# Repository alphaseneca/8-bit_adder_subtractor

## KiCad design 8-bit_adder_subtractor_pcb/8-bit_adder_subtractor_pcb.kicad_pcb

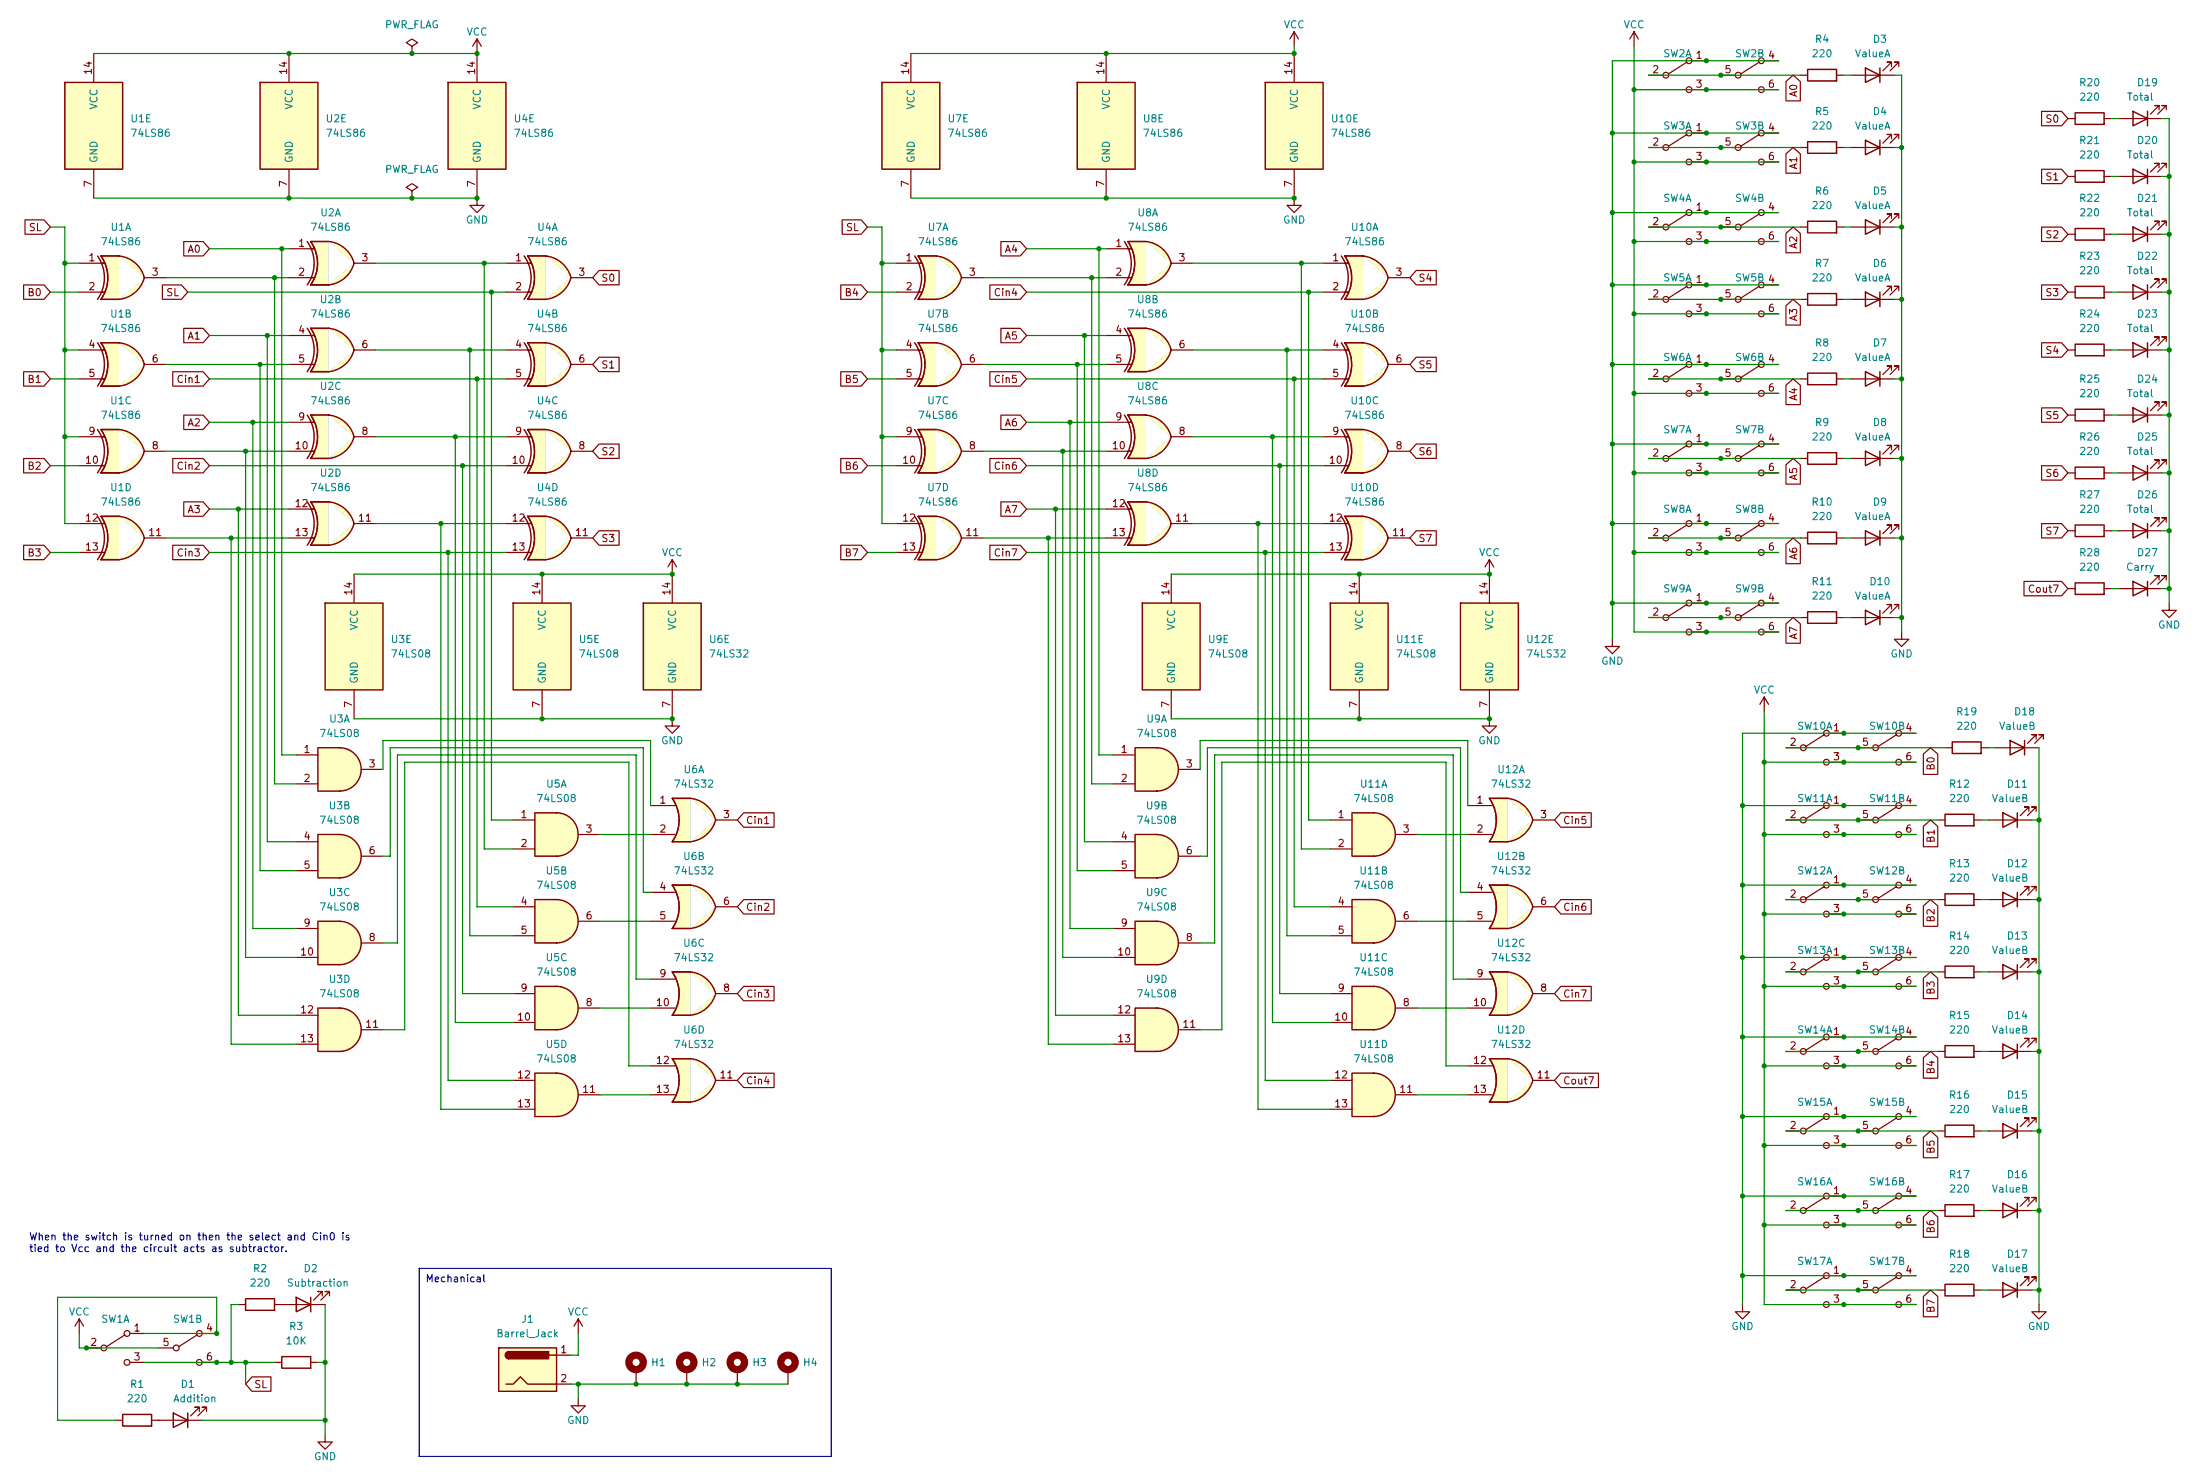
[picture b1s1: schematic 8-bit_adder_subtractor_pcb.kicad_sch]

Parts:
D1: Addition; LED_D3.0mm
D2: Subtraction; LED_D3.0mm
D3, D4, D5, D6, D7, D8, D9, D10: ValueA; LED_D3.0mm
D11, D12, D13, D14, D15, D16, D17, D18: ValueB; LED_D3.0mm
D19, D20, D21, D22, D23, D24, D25, D26: Total; LED_D3.0mm
D27: Carry; LED_D3.0mm
H1, H2, H3, H4: MountingHole_Pad; MountingHole_3mm_Pad
J1: Barrel_Jack; BarrelJack_Horizontal
R1, R2, R4, R5, R6, R7, R8, R9, R10, R11, R12, R13, R14, R15, R16, R17, R18, R19, R20, R21, R22, R23, R24, R25, R26, R27, R28: 220; R_Axial_DIN0207_L6.3mm_D2.5mm_P7.62mm_Horizontal
R3: 10K; R_Axial_DIN0207_L6.3mm_D2.5mm_P7.62mm_Horizontal
SW1, SW2, SW3, SW4, SW5, SW6, SW7, SW8, SW9, SW10, SW11, SW12, SW13, SW14, SW15, SW16, SW17: SW_DPDT_x2; SWITCH_S20203
U1, U2, U4, U7, U8, U10: 74LS86; DIP-14_W7.62mm
U3, U5, U9, U11: 74LS08; DIP-14_W7.62mm
U6, U12: 74LS32; DIP-14_W7.62mm

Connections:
A0: R4.1, SW2.2 (B), SW2.5 (B), U2.1, U3.1; also elsewhere on the board
A1: R5.1, SW3.2 (B), SW3.5 (B), U2.4, U3.4; also elsewhere on the board
A2: R6.1, SW4.2 (B), SW4.5 (B), U2.9, U3.9; also elsewhere on the board
A3: R7.1, SW5.2 (B), SW5.5 (B), U2.12, U3.12; also elsewhere on the board
A4: R8.1, SW6.2 (B), SW6.5 (B), U8.1, U9.1; also elsewhere on the board
A5: R9.1, SW7.2 (B), SW7.5 (B), U8.4, U9.4; also elsewhere on the board
A6: R10.1, SW8.2 (B), SW8.5 (B), U8.9, U9.9; also elsewhere on the board
A7: R11.1, SW9.2 (B), SW9.5 (B), U8.12, U9.12; also elsewhere on the board
B0: R19.1, SW10.2 (B), SW10.5 (B), U1.2; also elsewhere on the board
B1: R12.1, SW11.2 (B), SW11.5 (B), U1.5; also elsewhere on the board
B2: R13.1, SW12.2 (B), SW12.5 (B), U1.10; also elsewhere on the board
B3: R14.1, SW13.2 (B), SW13.5 (B), U1.13; also elsewhere on the board
B4: R15.1, SW14.2 (B), SW14.5 (B), U7.2; also elsewhere on the board
B5: R16.1, SW15.2 (B), SW15.5 (B), U7.5; also elsewhere on the board
B6: R17.1, SW16.2 (B), SW16.5 (B), U7.10; also elsewhere on the board
B7: R18.1, SW17.2 (B), SW17.5 (B), U7.13; also elsewhere on the board
Cin1: U4.5, U5.4, U6.3; also elsewhere on the board
Cin2: U4.10, U5.9, U6.6; also elsewhere on the board
Cin3: U4.13, U5.12, U6.8; also elsewhere on the board
Cin4: U6.11, U10.2, U11.1; also elsewhere on the board
Cin5: U10.5, U11.4, U12.3; also elsewhere on the board
Cin6: U10.10, U11.9, U12.6; also elsewhere on the board
Cin7: U10.13, U11.12, U12.8; also elsewhere on the board
Cout7: R28.1, U12.11; also elsewhere on the board
GND: D1.1 (K), D2.1 (K), D3.1 (K), D4.1 (K), D5.1 (K), D6.1 (K), D7.1 (K), D8.1 (K), D9.1 (K), D10.1 (K), D11.1 (K), D12.1 (K), D13.1 (K), D14.1 (K), D15.1 (K), D16.1 (K), D17.1 (K), D18.1 (K), D19.1 (K), D20.1 (K), D21.1 (K), D22.1 (K), D23.1 (K), D24.1 (K), D25.1 (K), D26.1 (K), D27.1 (K), H1.1, H2.1, H3.1, H4.1, J1.2, R3.2, SW2.1 (A), SW2.4 (A), SW3.1 (A), SW3.4 (A), SW4.1 (A), SW4.4 (A), SW5.1 (A), SW5.4 (A), SW6.1 (A), SW6.4 (A), SW7.1 (A), SW7.4 (A), SW8.1 (A), SW8.4 (A), SW9.1 (A), SW9.4 (A), SW10.1 (A), SW10.4 (A), SW11.1 (A), SW11.4 (A), SW12.1 (A), SW12.4 (A), SW13.1 (A), SW13.4 (A), SW14.1 (A), SW14.4 (A), SW15.1 (A), SW15.4 (A), SW16.1 (A), SW16.4 (A), SW17.1 (A), SW17.4 (A), U1.7 (GND), U2.7 (GND), U3.7 (GND), U4.7 (GND), U5.7 (GND), U6.7 (GND), U7.7 (GND), U8.7 (GND), U9.7 (GND), U10.7 (GND), U11.7 (GND), U12.7 (GND); also elsewhere on the board
unnamed: D1.2 (A), R1.2
unnamed: D2.2 (A), R2.2
unnamed: D3.2 (A), R4.2
unnamed: D4.2 (A), R5.2
unnamed: D5.2 (A), R6.2
unnamed: D6.2 (A), R7.2
unnamed: D7.2 (A), R8.2
unnamed: D8.2 (A), R9.2
unnamed: D9.2 (A), R10.2
unnamed: D10.2 (A), R11.2
unnamed: D11.2 (A), R12.2
unnamed: D12.2 (A), R13.2
unnamed: D13.2 (A), R14.2
unnamed: D14.2 (A), R15.2
unnamed: D15.2 (A), R16.2
unnamed: D16.2 (A), R17.2
unnamed: D17.2 (A), R18.2
unnamed: D18.2 (A), R19.2
unnamed: D19.2 (A), R20.2
unnamed: D20.2 (A), R21.2
unnamed: D21.2 (A), R22.2
unnamed: D22.2 (A), R23.2
unnamed: D23.2 (A), R24.2
unnamed: D24.2 (A), R25.2
unnamed: D25.2 (A), R26.2
unnamed: D26.2 (A), R27.2
unnamed: D27.2 (A), R28.2
unnamed: R1.1, SW1.1 (A), SW1.4 (A)
unnamed 53: U1.3, U2.2, U3.2; also elsewhere on the board
unnamed 54: U1.6, U2.5, U3.5; also elsewhere on the board
unnamed 55: U1.8, U2.10, U3.10; also elsewhere on the board
unnamed 56: U1.11, U2.13, U3.13; also elsewhere on the board
unnamed 57: U2.3, U4.1, U5.2; also elsewhere on the board
unnamed 58: U2.6, U4.4, U5.5; also elsewhere on the board
unnamed 59: U2.8, U4.9, U5.10; also elsewhere on the board
unnamed 60: U2.11, U4.12, U5.13; also elsewhere on the board
unnamed 61: U3.3, U6.1; also elsewhere on the board
unnamed 62: U3.6, U6.4; also elsewhere on the board
unnamed 63: U3.8, U6.9; also elsewhere on the board
unnamed 64: U3.11, U6.12; also elsewhere on the board
unnamed 65: U5.3, U6.2; also elsewhere on the board
unnamed 66: U5.6, U6.5; also elsewhere on the board
unnamed 67: U5.8, U6.10; also elsewhere on the board
unnamed 68: U5.11, U6.13; also elsewhere on the board
unnamed 69: U7.3, U8.2, U9.2; also elsewhere on the board
unnamed 70: U7.6, U8.5, U9.5; also elsewhere on the board
unnamed 71: U7.8, U8.10, U9.10; also elsewhere on the board
unnamed 72: U7.11, U8.13, U9.13; also elsewhere on the board
unnamed 73: U8.3, U10.1, U11.2; also elsewhere on the board
unnamed 74: U8.6, U10.4, U11.5; also elsewhere on the board
unnamed 75: U8.8, U10.9, U11.10; also elsewhere on the board
unnamed 76: U8.11, U10.12, U11.13; also elsewhere on the board
unnamed 77: U11.3, U12.2; also elsewhere on the board
unnamed 78: U11.6, U12.5; also elsewhere on the board
unnamed 79: U11.8, U12.10; also elsewhere on the board
unnamed 80: U11.11, U12.13; also elsewhere on the board
unnamed 81: U9.3, U12.1; also elsewhere on the board
unnamed 82: U9.6, U12.4; also elsewhere on the board
unnamed 83: U9.8, U12.9; also elsewhere on the board
unnamed 84: U9.11, U12.12; also elsewhere on the board
S0: R20.1, U4.3; also elsewhere on the board
S1: R21.1, U4.6; also elsewhere on the board
S2: R22.1, U4.8; also elsewhere on the board
S3: R23.1, U4.11; also elsewhere on the board
S4: R24.1, U10.3; also elsewhere on the board
S5: R25.1, U10.6; also elsewhere on the board
S6: R26.1, U10.8; also elsewhere on the board
S7: R27.1, U10.11; also elsewhere on the board
SL: R2.1, R3.1, SW1.3 (C), SW1.6 (C), U1.1, U1.4, U1.9, U1.12, U4.2, U5.1, U7.1, U7.4, U7.9, U7.12; also elsewhere on the board
VCC: J1.1, SW1.2 (B), SW1.5 (B), SW2.3 (C), SW2.6 (C), SW3.3 (C), SW3.6 (C), SW4.3 (C), SW4.6 (C), SW5.3 (C), SW5.6 (C), SW6.3 (C), SW6.6 (C), SW7.3 (C), SW7.6 (C), SW8.3 (C), SW8.6 (C), SW9.3 (C), SW9.6 (C), SW10.3 (C), SW10.6 (C), SW11.3 (C), SW11.6 (C), SW12.3 (C), SW12.6 (C), SW13.3 (C), SW13.6 (C), SW14.3 (C), SW14.6 (C), SW15.3 (C), SW15.6 (C), SW16.3 (C), SW16.6 (C), SW17.3 (C), SW17.6 (C), U1.14 (VCC), U2.14 (VCC), U3.14 (VCC), U4.14 (VCC), U5.14 (VCC), U6.14 (VCC), U7.14 (VCC), U8.14 (VCC), U9.14 (VCC), U10.14 (VCC), U11.14 (VCC), U12.14 (VCC); also elsewhere on the board

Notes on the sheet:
Mechanical
When the switch is turned on then the select and Cin0 is tied to Vcc and the circuit acts as subtractor.

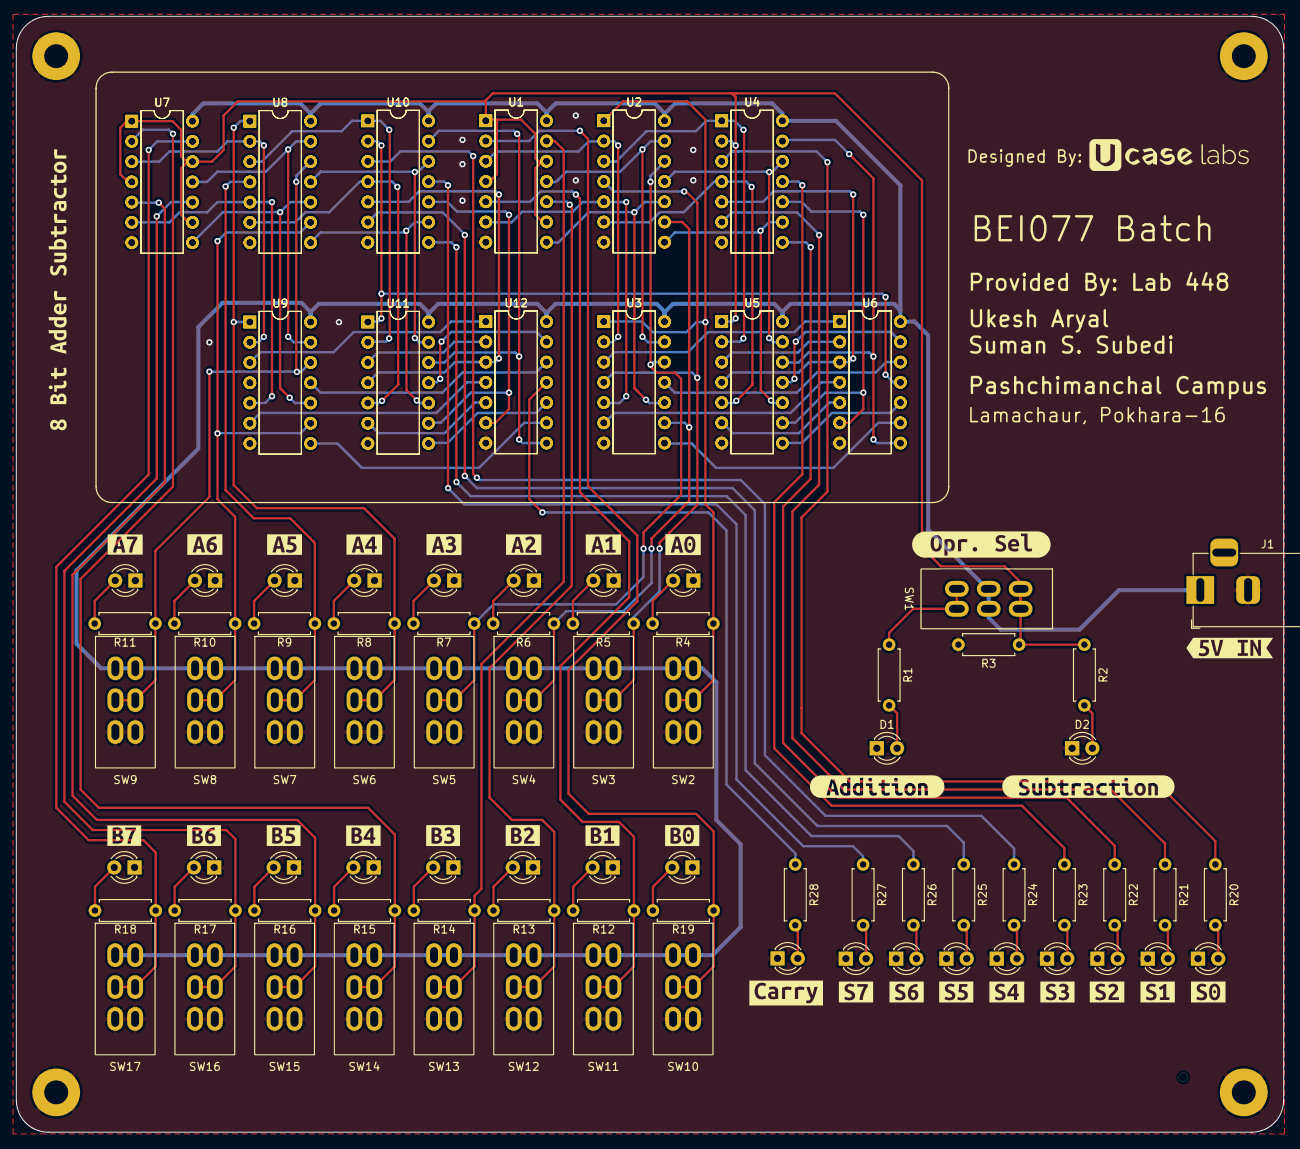
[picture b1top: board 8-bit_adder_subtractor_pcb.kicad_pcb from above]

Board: 2 copper layers, 159.0 x 140.0 mm, 131 parts (0 on the bottom side), 95 nets.

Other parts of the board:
U1#2, U2#2, U4#2, U7#2, U8#2, U10#2: 74LS86; DIP-14_W7.62mm
U3#2, U5#2, U9#2, U11#2: 74LS08; DIP-14_W7.62mm
U6#2, U12#2: 74LS32; DIP-14_W7.62mm
kibuzzard-6723CCFE: G***; kibuzzard-6723CCFE
kibuzzard-6723CD0E: G***; kibuzzard-6723CD0E
kibuzzard-6723CD1A: G***; kibuzzard-6723CD1A
kibuzzard-6723CD2D: G***; kibuzzard-6723CD2D
kibuzzard-6723CD06: G***; kibuzzard-6723CD06
kibuzzard-6723CD14: G***; kibuzzard-6723CD14
kibuzzard-6723CD21: G***; kibuzzard-6723CD21
kibuzzard-6723CD27: G***; kibuzzard-6723CD27
kibuzzard-6723D2BC: G***; kibuzzard-6723D2BC
kibuzzard-6723D2C8: G***; kibuzzard-6723D2C8
kibuzzard-6723D2CE: G***; kibuzzard-6723D2CE
kibuzzard-6723D2D3: G***; kibuzzard-6723D2D3
kibuzzard-6723D2DF: G***; kibuzzard-6723D2DF
kibuzzard-6723D2E6: G***; kibuzzard-6723D2E6
kibuzzard-6723D2EE: G***; kibuzzard-6723D2EE
kibuzzard-6723D31B: G***; kibuzzard-6723D31B
kibuzzard-6723D320: G***; kibuzzard-6723D320
kibuzzard-6723D341: G***; kibuzzard-6723D341
kibuzzard-68098BF2: G***; kibuzzard-68098BF2
kibuzzard-672327BC: G***; kibuzzard-672327BC
kibuzzard-672327C5: G***; kibuzzard-672327C5
kibuzzard-672327D0: G***; kibuzzard-672327D0
kibuzzard-672327D8: G***; kibuzzard-672327D8
kibuzzard-672327DE: G***; kibuzzard-672327DE
kibuzzard-672327E5: G***; kibuzzard-672327E5
kibuzzard-672327EF: G***; kibuzzard-672327EF
kibuzzard-672491A3: G***; kibuzzard-672491A3
kibuzzard-6723279E: G***; kibuzzard-6723279E
kibuzzard-6723280D: G***; kibuzzard-6723280D
kibuzzard-67232848: G***; kibuzzard-67232848

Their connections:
A0: U2#2.1, U3#2.1; also elsewhere on the board
A1: U2#2.4, U3#2.4; also elsewhere on the board
A2: U2#2.9, U3#2.9; also elsewhere on the board
A3: U2#2.12, U3#2.12; also elsewhere on the board
A4: U8#2.1, U9#2.1; also elsewhere on the board
A5: U8#2.4, U9#2.4; also elsewhere on the board
A6: U8#2.9, U9#2.9; also elsewhere on the board
A7: U8#2.12, U9#2.12; also elsewhere on the board
B0: U1#2.2; also elsewhere on the board
B1: U1#2.5; also elsewhere on the board
B2: U1#2.10; also elsewhere on the board
B3: U1#2.13; also elsewhere on the board
B4: U7#2.2; also elsewhere on the board
B5: U7#2.5; also elsewhere on the board
B6: U7#2.10; also elsewhere on the board
B7: U7#2.13; also elsewhere on the board
Cin1: U4#2.5, U5#2.4, U6#2.3; also elsewhere on the board
Cin2: U4#2.10, U5#2.9, U6#2.6; also elsewhere on the board
Cin3: U4#2.13, U5#2.12, U6#2.8; also elsewhere on the board
Cin4: U6#2.11, U10#2.2, U11#2.1; also elsewhere on the board
Cin5: U10#2.5, U11#2.4, U12#2.3; also elsewhere on the board
Cin6: U10#2.10, U11#2.9, U12#2.6; also elsewhere on the board
Cin7: U10#2.13, U11#2.12, U12#2.8; also elsewhere on the board
Cout7: U12#2.11; also elsewhere on the board
GND: U1#2.7 (GND), U2#2.7 (GND), U3#2.7 (GND), U4#2.7 (GND), U5#2.7 (GND), U6#2.7 (GND), U7#2.7 (GND), U8#2.7 (GND), U9#2.7 (GND), U10#2.7 (GND), U11#2.7 (GND), U12#2.7 (GND); also elsewhere on the board
unnamed 53: U1#2.3, U2#2.2, U3#2.2; also elsewhere on the board
unnamed 54: U1#2.6, U2#2.5, U3#2.5; also elsewhere on the board
unnamed 55: U1#2.8, U2#2.10, U3#2.10; also elsewhere on the board
unnamed 56: U1#2.11, U2#2.13, U3#2.13; also elsewhere on the board
unnamed 57: U2#2.3, U4#2.1, U5#2.2; also elsewhere on the board
unnamed 58: U2#2.6, U4#2.4, U5#2.5; also elsewhere on the board
unnamed 59: U2#2.8, U4#2.9, U5#2.10; also elsewhere on the board
unnamed 60: U2#2.11, U4#2.12, U5#2.13; also elsewhere on the board
unnamed 61: U3#2.3, U6#2.1; also elsewhere on the board
unnamed 62: U3#2.6, U6#2.4; also elsewhere on the board
unnamed 63: U3#2.8, U6#2.9; also elsewhere on the board
unnamed 64: U3#2.11, U6#2.12; also elsewhere on the board
unnamed 65: U5#2.3, U6#2.2; also elsewhere on the board
unnamed 66: U5#2.6, U6#2.5; also elsewhere on the board
unnamed 67: U5#2.8, U6#2.10; also elsewhere on the board
unnamed 68: U5#2.11, U6#2.13; also elsewhere on the board
unnamed 69: U7#2.3, U8#2.2, U9#2.2; also elsewhere on the board
unnamed 70: U7#2.6, U8#2.5, U9#2.5; also elsewhere on the board
unnamed 71: U7#2.8, U8#2.10, U9#2.10; also elsewhere on the board
unnamed 72: U7#2.11, U8#2.13, U9#2.13; also elsewhere on the board
unnamed 73: U8#2.3, U10#2.1, U11#2.2; also elsewhere on the board
unnamed 74: U8#2.6, U10#2.4, U11#2.5; also elsewhere on the board
unnamed 75: U8#2.8, U10#2.9, U11#2.10; also elsewhere on the board
unnamed 76: U8#2.11, U10#2.12, U11#2.13; also elsewhere on the board
unnamed 77: U11#2.3, U12#2.2; also elsewhere on the board
unnamed 78: U11#2.6, U12#2.5; also elsewhere on the board
unnamed 79: U11#2.8, U12#2.10; also elsewhere on the board
unnamed 80: U11#2.11, U12#2.13; also elsewhere on the board
unnamed 81: U9#2.3, U12#2.1; also elsewhere on the board
unnamed 82: U9#2.6, U12#2.4; also elsewhere on the board
unnamed 83: U9#2.8, U12#2.9; also elsewhere on the board
unnamed 84: U9#2.11, U12#2.12; also elsewhere on the board
S0: U4#2.3; also elsewhere on the board
S1: U4#2.6; also elsewhere on the board
S2: U4#2.8; also elsewhere on the board
S3: U4#2.11; also elsewhere on the board
S4: U10#2.3; also elsewhere on the board
S5: U10#2.6; also elsewhere on the board
S6: U10#2.8; also elsewhere on the board
S7: U10#2.11; also elsewhere on the board
SL: U1#2.1, U1#2.4, U1#2.9, U1#2.12, U4#2.2, U5#2.1, U7#2.1, U7#2.4, U7#2.9, U7#2.12; also elsewhere on the board
VCC: U1#2.14 (VCC), U2#2.14 (VCC), U3#2.14 (VCC), U4#2.14 (VCC), U5#2.14 (VCC), U6#2.14 (VCC), U7#2.14 (VCC), U8#2.14 (VCC), U9#2.14 (VCC), U10#2.14 (VCC), U11#2.14 (VCC), U12#2.14 (VCC); also elsewhere on the board

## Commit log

2023-12-29 Initialized pcb schematics design
2023-12-31 Redesigned DDPT switch footprint
2024-10-20 added the pcb files
2024-10-20 added the readme
2025-04-24 Edited the Silkscreen for LAB448
2025-04-24 cleaned and organized
